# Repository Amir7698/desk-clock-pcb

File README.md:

# Round Desk Companion (desk-clock-pcb)

A small round desk gadget (clock / weather / room sensor), designed as a first
KiCad 9 project: a 2-layer, 55 mm round PCB around an ESP32-C3 module, powered
over USB-C or a LiPo cell.

**Status:** schematic complete (ERC clean), PCB laid out and routed, DRC being
finished. Not fabricated yet — no hardware results are claimed here.

## Preview

3D renders generated with `kicad-cli` from the current board state (work in progress).

Bottom side (ground pour, a few hop routes; all parts are on top):

Schematic: [docs/desk-clock-schematic.pdf](docs/desk-clock-schematic.pdf)

## What is on the board

| Block | Part | Notes |
|---|---|---|
| MCU + radio | ESP32-C3-WROOM-02 | Wi-Fi, native USB on IO18/IO19, antenna at the board edge with copper keep-out |
| USB | USB-C receptacle | 5.1 k on CC1/CC2 (sink), D+/D- tied across both orientations |
| Charger | MCP73831 | ~500 mA (R-PROG 2 k), charge LED on STAT |
| Power path | 2x Schottky diode-OR | USB (VBUS) or battery -> VSYS |
| Regulator | AP2112K-3.3 | LDO, VSYS -> +3V3 |
| Display | 8-pin 2.54 mm header | 1.28" round GC9A01 over SPI (cable) |
| Sensor | BME280 | I2C, 4.7 k pull-ups |
| Input | Rotary encoder + push | pull-ups on A/B/SW |
| Battery sense | 100 k / 100 k divider | to ADC (IO3) |

### GPIO map

| Pin | Function | Pin | Function |
|---|---|---|---|
| IO0 | I2C_SCL | IO8 | DISP_BL |
| IO1 | I2C_SDA | IO9 | BOOT button |
| IO2 | ENC_SW | IO10 | DISP_RST |
| IO3 | BAT_SENSE | IO18 | USB D- |
| IO4 | DISP_SCK | IO19 | USB D+ |
| IO5 | DISP_MOSI | IO20 | ENC_A |
| IO6 | DISP_CS | IO21 | ENC_B |
| IO7 | DISP_DC | | |

## Layout notes

- 2 layers, GND pour on both; antenna end of the module placed at the board edge
  with a copper/track/via keep-out underneath.
- Net class `Power` (0.5 mm) for VBUS, +BATT, VSYS, +3V3; 0.2 mm elsewhere.
- Rules chosen to stay inside JLCPCB 2-layer limits (0.2 mm clearance, 0.6/0.3 mm vias).
- Critical nets were routed by hand; the remainder with FreeRouting, then cleaned
  up (stray vias and stubs removed, track widths raised to the 0.2 mm rule).

## Known limitations / what I would change

- Two layers get crowded around the USB-C connector and the charger; a 4-layer
  stack-up (signal / GND / power / signal) would let USB and the display bus run
  without vias.
- The LDO drops ~1.4 V from USB: fine on average Wi-Fi load, but a buck converter
  would run cooler (rev B).
- No ESD protection on the USB data lines and no battery-side fuse (rev B).
- The ESP32 module footprint has nine 0.2 mm thermal vias, below the 0.3 mm DRC
  minimum I set; to be revisited before ordering.

## Files

- `desk-clock.kicad_pro / .kicad_sch / .kicad_pcb` — KiCad 9 project
- `scripts/` — small KiCad scripting-console helpers used for placement
- `docs/` — schematic PDF and 3D renders

Open the `.kicad_pro` in KiCad 9.

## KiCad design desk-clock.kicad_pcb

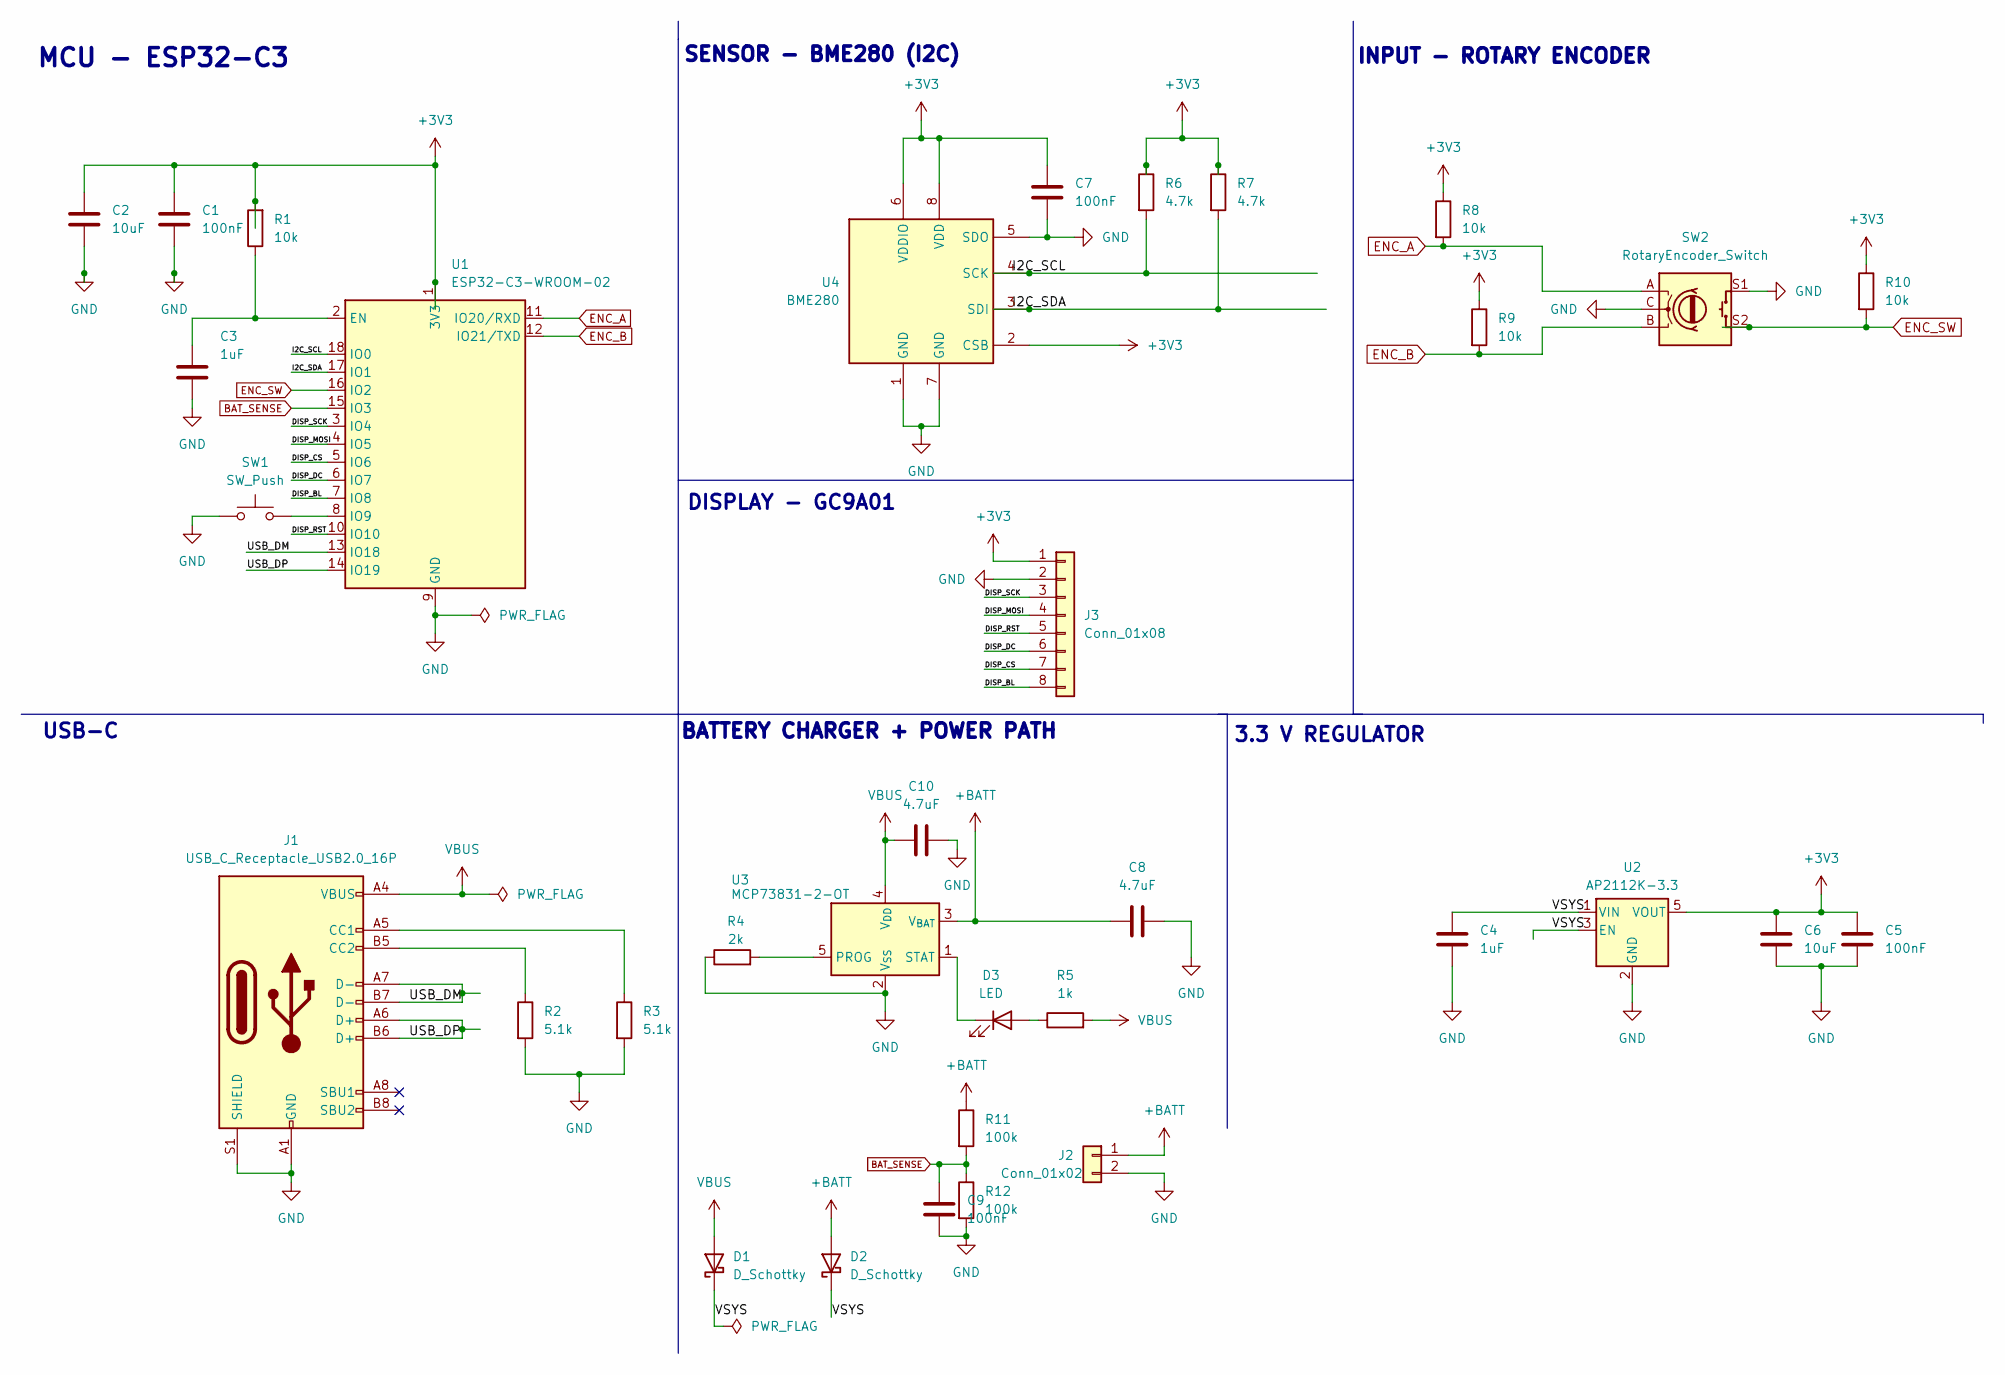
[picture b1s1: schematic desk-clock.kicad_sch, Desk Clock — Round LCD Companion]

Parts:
C1, C5, C7, C9: 100nF; C_0603_1608Metric
C2, C6: 10uF; C_0805_2012Metric
C3, C4: 1uF; C_0603_1608Metric
C8, C10: 4.7uF; C_0603_1608Metric
D1, D2: D_Schottky; D_SOD-123
D3: LED; LED_0603_1608Metric
J1: USB_C_Receptacle_USB2.0_16P; USB_C_Receptacle_HRO_TYPE-C-31-M-12
J2: Conn_01x02; JST_PH_B2B-PH-K_1x02_P2.00mm_Vertical
J3: Conn_01x08; PinHeader_1x08_P2.54mm_Vertical
R1, R8, R9, R10: 10k; R_0603_1608Metric
R2, R3: 5.1k; R_0603_1608Metric
R4: 2k; R_0603_1608Metric
R5: 1k; R_0603_1608Metric
R6, R7: 4.7k; R_0603_1608Metric
R11, R12: 100k; R_0603_1608Metric
SW1: SW_Push; SW_SPST_TL3342
SW2: RotaryEncoder_Switch; RotaryEncoder_Alps_EC11E-Switch_Vertical_H20mm
U1: ESP32-C3-WROOM-02
U2: AP2112K-3.3; SOT-23-5
U3: MCP73831-2-OT; SOT-23-5
U4: BME280; Bosch_LGA-8_2.5x2.5mm_P0.65mm_ClockwisePinNumbering

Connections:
+3V3: C1.1, C2.1, C5.1, C6.1, C7.1, J3.1, R1.2, R6.1, R7.1, R8.1, R9.1, R10.1, U1.1 (3V3), U2.5 (VOUT), U4.2 (CSB), U4.6 (VDDIO), U4.8 (VDD)
+BATT: C8.1, D2.2 (A), J2.1, R11.1, U3.3 (V_{BAT})
/DISP_BL: J3.8, U1.7 (IO8)
/DISP_CS: J3.7, U1.5 (IO6)
/DISP_DC: J3.6, U1.6 (IO7)
/DISP_MOSI: J3.4, U1.4 (IO5)
/DISP_RST: J3.5, U1.10 (IO10)
/DISP_SCK: J3.3, U1.3 (IO4)
/I2C_SCL: R6.2, U1.18 (IO0), U4.4 (SCK)
/I2C_SDA: R7.2, U1.17 (IO1), U4.3 (SDI)
/USB_DM: J1.A7 (D-), J1.B7 (D-), U1.13 (IO18)
/USB_DP: J1.A6 (D+), J1.B6 (D+), U1.14 (IO19)
/VSYS: C4.1, D1.1 (K), D2.1 (K), U2.1 (VIN), U2.3 (EN)
BAT_SENSE: C9.1, R11.2, R12.1, U1.15 (IO3)
ENC_A: R8.2, SW2.A, U1.11 (IO20/RXD)
ENC_B: R9.2, SW2.B, U1.12 (IO21/TXD)
ENC_SW: R10.2, SW2.S2, U1.16 (IO2)
GND: C1.2, C2.2, C3.2, C4.2, C5.2, C6.2, C7.2, C8.2, C9.2, C10.2, J1.A1 (GND), J1.A12 (GND), J1.B1 (GND), J1.B12 (GND), J1.S1 (SHIELD), J2.2, J3.2, R2.2, R3.2, R4.1, R12.2, SW1.1, SW2.C, SW2.S1, U1.9 (GND), U1.19 (GND), U2.2 (GND), U3.2 (V_{SS}), U4.1 (GND), U4.5 (SDO), U4.7 (GND)
unnamed: D3.2 (A), R5.1
unnamed: D3.1 (K), U3.1 (STAT)
unnamed: J1.A5 (CC1), R3.1
unnamed: J1.B5 (CC2), R2.1
unnamed: C3.1, R1.1, U1.2 (EN)
unnamed: SW1.2, U1.8 (IO9)
unnamed: R4.2, U3.5 (PROG)
VBUS: C10.1, D1.2 (A), J1.A4 (VBUS), J1.A9 (VBUS), J1.B4 (VBUS), J1.B9 (VBUS), R5.2, U3.4 (V_{DD})

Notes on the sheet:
USB-C
MCU - ESP32-C3
DISPLAY - GC9A01
SENSOR - BME280 (I2C)
BATTERY CHARGER + POWER PATH
3.3 V REGULATOR
INPUT - ROTARY ENCODER

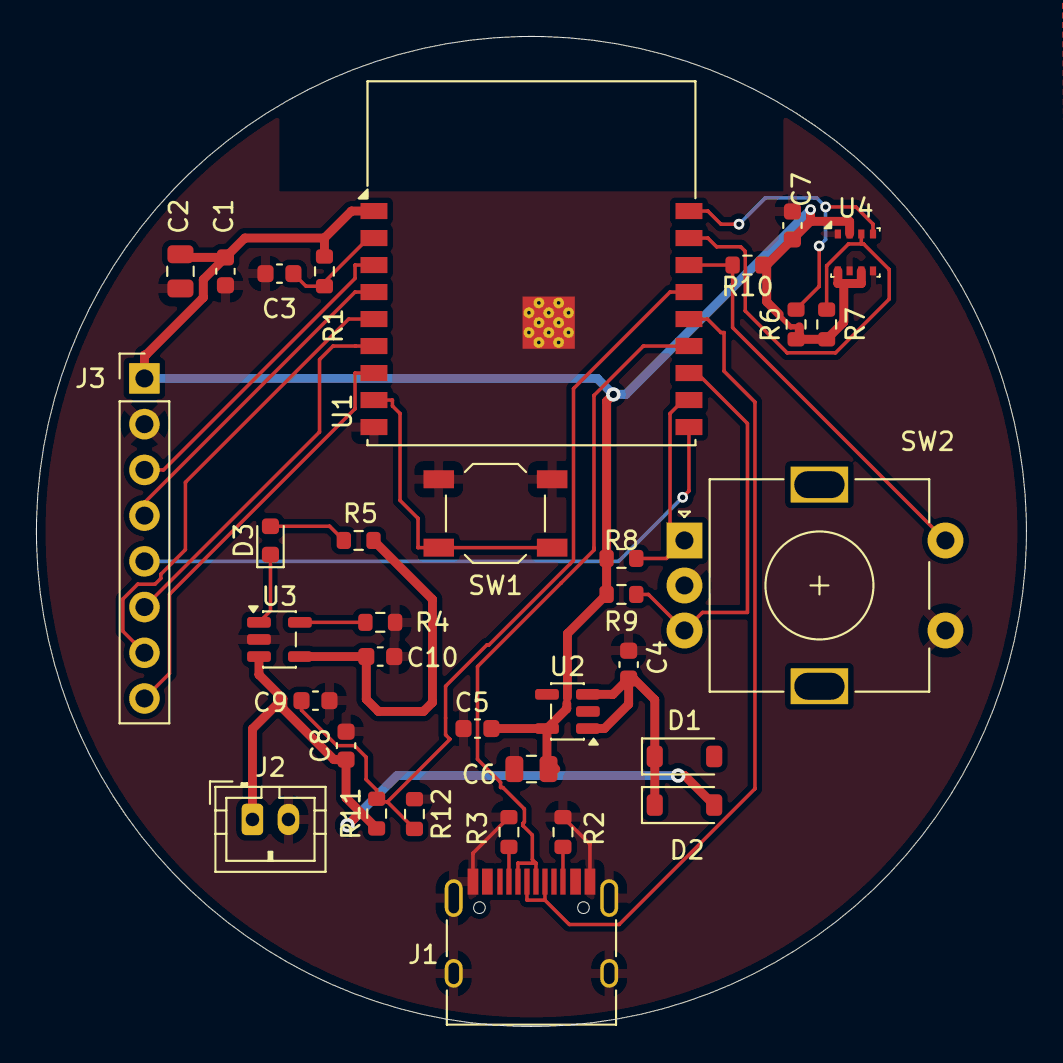
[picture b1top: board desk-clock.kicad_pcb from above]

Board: 2 copper layers, 55.0 x 55.0 mm, 34 parts (0 on the bottom side), 26 nets.
